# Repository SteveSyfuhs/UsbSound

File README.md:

# Usb Sound
 A custom-made USB sound card for Balanced Audio.

# Why?

My current USB DAC isn't great and instead of just buying a new one I thought I'd try and waste some serious engineering hours learning how to build one instead.

# What's wrong with the current DAC?

My existing DAC uses the [PCM2705](https://www.ti.com/lit/ds/symlink/pcm2705.pdf) chip to handle both the USB and DAC side of things. It's fine, I guess, but it has some annoying quirks.

First, you have to bolt on an additional chip to do silly things like control the USB descriptors. Absent that you're left with this annoying string with two trailing spaces (probably nulls?). Clearly not the end of the world, but I might as well aim for perfect.

Second, the output from the chip is only single-ended so it requires extra effort to make a _good_ differential output. This existing device is using a transformer (two, on per channel) to generate the differential pair, which is great for isolation, but transformers are notorious for distortion at high frequency. 

Curiously this device also doesn't produce a great differential output at 1000hz.

Channel A (blue) is the positive leg and Channel B (red) is the negative leg. Channel 3 (magenta?) is A+B, which ideally should sum to zero, not ~16mV RMS.

# Why are you using X?

To be clear: I really have no idea what I'm doing so my choice of parts or circuit are driven by the last thing I learned about. If there's clearly a better way to do something then please let me know.

### Why the STM32F4 Micro?

It happened to be the chip used in [Phil's video](https://www.youtube.com/watch?v=C7-8nUU6e3E) where learned to use Kicad and it happens to support I2S. It's incredibly powerful for the use case here, and a less powerful device could be used instead. That said, it could make for a useful platform for building out digital filters and stuff.

### Why the [PCM1795](https://www.ti.com/lit/ds/symlink/pcm1795.pdf) DAC?

I like the low distortion and noise floor it provides and since I'm starting with a blank canvas why not start with something that's overkill? I can only make it worse.

Note: the _audible_ differences between this and other DACs is ultimately going to be nil so there will be no notable benefit. I'm doing this because I can.

### Why the [NE5524](https://www.ti.com/lit/ds/symlink/ne5534.pdf) Op-Amps?

The PCM1795 uses that as a baseline for the measured circuits so it's a helpful starting place. I will probably switch these out for [LM4562's](https://www.ti.com/lit/ds/symlink/lm4562.pdf) in the near future once I test out the board and do initial measurements to compare against spec. The LM4562s have lower distortion and noise floor, and more interestingly contain two op-amps in the package so I can reduce the circuit footprint.

Again, I can only make things worse.

### Why Balanced Audio?

The speakers I'll be driving are studio monitors and they require a balanced XLR connection.

## Are you going to support multiple output channels?

Eventually, probably. The micro supports 3 I2S lines, and each I2S line supports two channels out and one in.

## Are you going to support audio in?

Maybe. See the output section.

## What's the driver story?

Ideally it'll show up as a USB audio device and all major operating systems will just pick it up.

# Measurement Methodology

A work in progress. Ideal testing should measure:

 * Noise - Specifically what the device adds to the signal.
 * Distortion - Specifically how the device modifies the signal integrity across the device bandwidth.
 * Flatness - Specifically whether the device has amplified or attenuated voltage across the device bandwidth.

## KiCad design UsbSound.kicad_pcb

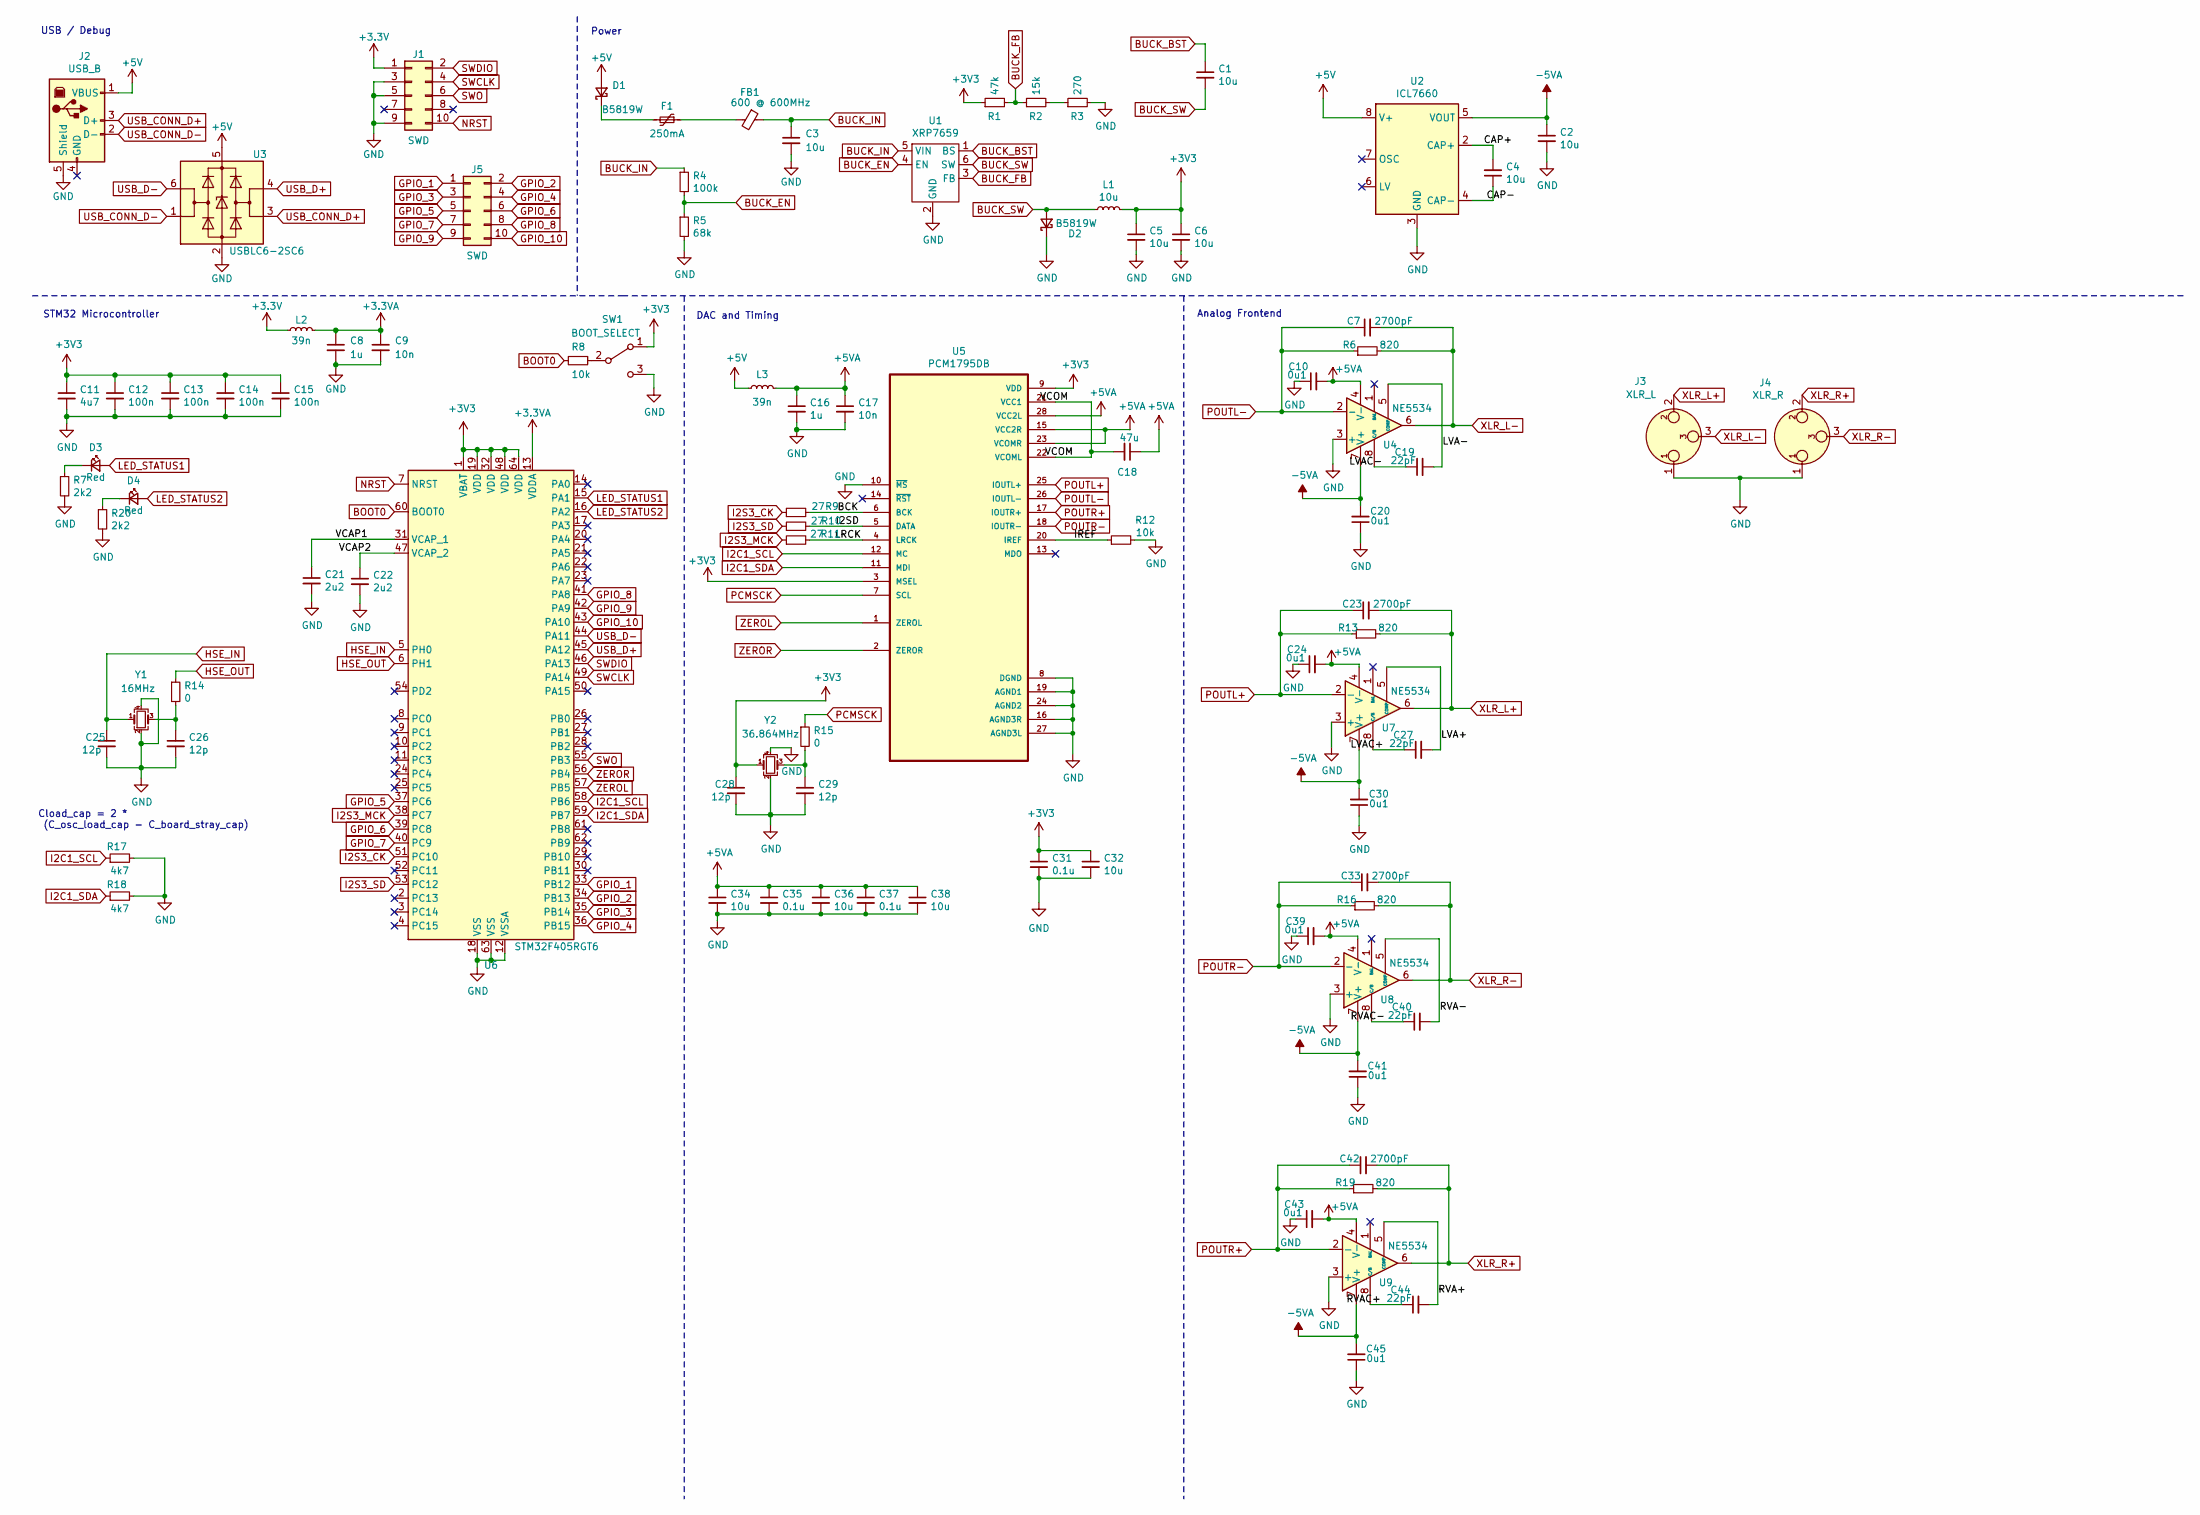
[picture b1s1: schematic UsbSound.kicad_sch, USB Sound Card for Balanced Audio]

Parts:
C1, C2, C4, C5, C6, C32, C34, C36, C38: 10u; C_1206_3216Metric
C3: 10u; C_1206_3216Metric; LCSC Part # C13585
C7, C23, C33, C42: 2700pF; C_1206_3216Metric
C8: 1u; C_1206_3216Metric; LCSC Part # C52923
C9: 10n; C_1206_3216Metric; LCSC Part # C15195
C10, C20, C24, C30, C39, C41, C43, C45: 0u1; C_1206_3216Metric
C11: 4u7; C_1206_3216Metric
C12, C13, C14, C15: 100n; C_1206_3216Metric
C16: 1u; C_1206_3216Metric
C17: 10n; C_1206_3216Metric
C18: 47u; C_1206_3216Metric
C19, C27, C40, C44: 22pF; C_1206_3216Metric
C21, C22: 2u2; C_1206_3216Metric
C25, C26, C28, C29: 12p; C_1206_3216Metric
C31, C35, C37: 0.1u; C_1206_3216Metric
D1: B5819W; D_SOD-123; LCSC Part # C8598
D2: B5819W; D_SOD-123
D3, D4: Red; LED_1206_3216Metric
F1: 250mA; Fuse_1206_3216Metric; LCSC Part # C369159
FB1: 600 @ 600MHz; L_0805_2012Metric; LCSC Part # C1017
J1, J5: SWD; PinHeader_2x05_P1.27mm_Vertical_SMD
J2: USB_B; USB_B_Lumberg_2411_02_Horizontal
J3: XLR_L; Jack_XLR_Neutrik_NC3MAH_Horizontal
J4: XLR_R; Jack_XLR_Neutrik_NC3MAH_Horizontal
L1: 10u; L_1206_3216Metric
L2: 39n; L_0402_1005Metric; LCSC Part # C26443
L3: 39n; L_1206_3216Metric
R1: 47k; R_1206_3216Metric
R2: 15k; R_1206_3216Metric
R3: 270; R_1206_3216Metric
R4: 100k; R_1206_3216Metric
R5: 68k; R_1206_3216Metric
R6, R13, R16, R19: 820; R_1206_3216Metric
R7, R20: 2k2; R_1206_3216Metric
R8, R12: 10k; R_1206_3216Metric
R9, R10, R11: 27; R_1206_3216Metric
R14, R15: 0; R_1206_3216Metric
R17, R18: 4k7; R_1206_3216Metric
SW1: BOOT_SELECT; SW_SPDT_PCM12
U1: XRP7659; TSOP-6_1.65x3.05mm_P0.95mm
U2: ICL7660; SOIC-8-1EP_3.9x4.9mm_P1.27mm_EP2.29x3mm
U3: USBLC6-2SC6; SOT-23-6; LCSC Part # C7519
U4, U7, U8, U9: NE5534; SOIC-8-1EP_3.9x4.9mm_P1.27mm_EP2.29x3mm
U5: PCM1795DB; SOP65P780X200-28N
U6: STM32F405RGT6; LQFP-64_10x10mm_P0.5mm
Y1: 16MHz; Crystal_SMD_3225-4Pin_3.2x2.5mm
Y2: 36.864MHz; Crystal_SMD_3225-4Pin_3.2x2.5mm

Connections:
+3.3VA: C8.1, C9.1, L2.2, U6.13 (VDDA)
+5V: D1.2 (A), J2.1 (VBUS), L3.1, U2.8 (V+), U3.5 (VBUS)
+5VA: C10.2, C16.1, C17.1, C18.1, C24.2, C34.1, C35.1, C36.1, C37.1, C38.1, C39.2, C43.2, L3.2, U4.4 (V-), U5.15 (VCC2R), U5.23 (VCOMR), U5.28 (VCC2L), U7.4 (V-), U8.4 (V-), U9.4 (V-)
-5VA: C2.1, C20.2, C30.2, C41.2, C45.2, U2.5 (VOUT), U4.7 (V+), U7.7 (V+), U8.7 (V+), U9.7 (V+)
/BCK: R9.2, U5.6 (BCK)
/CAP+: C4.2, U2.2 (CAP+)
/CAP-: C4.1, U2.4 (CAP-)
/I2SD: R10.2, U5.5 (DATA)
/IREF: R12.1, U5.20 (IREF)
/LRCK: R11.2, U5.4 (LRCK)
/LVA+: C27.2, U7.5 (COMP)
/LVA-: C19.2, U4.5 (COMP)
/LVAC+: C27.1, U7.8 (C/B)
/LVAC-: C19.1, U4.8 (C/B)
/RVA+: C44.2, U9.5 (COMP)
/RVA-: C40.2, U8.5 (COMP)
/RVAC+: C44.1, U9.8 (C/B)
/RVAC-: C40.1, U8.8 (C/B)
/VCAP1: C21.1, U6.31 (VCAP_1)
/VCAP2: C22.1, U6.47 (VCAP_2)
/VCOM: C18.2, U5.21 (VCC1), U5.22 (VCOML)
BOOT0: R8.2, U6.60 (BOOT0)
BUCK_BST: C1.1, U1.1 (BS)
BUCK_EN: R4.2, R5.1, U1.4 (EN)
BUCK_FB: R1.2, R2.1, U1.3 (FB)
BUCK_IN: C3.1, FB1.1, R4.1, U1.5 (VIN)
BUCK_SW: C1.2, D2.2 (A), L1.1, U1.6 (SW)
GND: C2.2, C3.2, C5.2, C6.2, C8.2, C9.2, C10.1, C11.2, C12.2, C13.2, C14.2, C15.2, C16.2, C17.2, C20.1, C21.2, C22.2, C24.1, C25.2, C26.2, C28.2, C29.2, C30.1, C31.2, C32.2, C34.2, C35.2, C36.2, C37.2, C38.2, C39.1, C41.1, C43.1, C45.1, D2.1 (K), J1.3, J1.5, J1.9, J2.5 (Shield), J3.1, J4.1, R3.2, R5.2, R7.2, R12.2, R17.2, R18.2, R20.2, SW1.3 (C), U1.2 (GND), U2.3 (GND), U3.2 (GND), U4.3 (+), U5.8 (DGND), U5.10 (~MS), U5.16 (AGND3R), U5.19 (AGND1), U5.24 (AGND2), U5.27 (AGND3L), U6.12 (VSSA), U6.18 (VSS), U6.63 (VSS), U7.3 (+), U8.3 (+), U9.3 (+), Y1.2, Y1.4, Y2.2, Y2.4
GPIO_1: J5.1, U6.33 (PB12)
GPIO_2: J5.2, U6.34 (PB13)
GPIO_3: J5.3, U6.35 (PB14)
GPIO_4: J5.4, U6.36 (PB15)
GPIO_5: J5.5, U6.37 (PC6)
GPIO_6: J5.6, U6.39 (PC8)
GPIO_7: J5.7, U6.40 (PC9)
GPIO_8: J5.8, U6.41 (PA8)
GPIO_9: J5.9, U6.42 (PA9)
GPIO_10: J5.10, U6.43 (PA10)
HSE_IN: C25.1, U6.5 (PH0), Y1.1
HSE_OUT: R14.1, U6.6 (PH1)
I2C1_SCL: R17.1, U5.12 (MC), U6.58 (PB6)
I2C1_SDA: R18.1, U5.11 (MDI), U6.59 (PB7)
I2S3_CK: R9.1, U6.51 (PC10)
I2S3_MCK: R11.1, U6.38 (PC7)
I2S3_SD: R10.1, U6.53 (PC12)
LED_STATUS1: D3.2 (A), U6.15 (PA1)
LED_STATUS2: D4.2 (A), U6.16 (PA2)
NRST: J1.10, U6.7 (NRST)
unnamed: C26.1, R14.2, Y1.3
unnamed: C29.1, R15.2, Y2.3
unnamed: D1.1 (K), F1.2
unnamed: D3.1 (K), R7.1
unnamed: D4.1 (K), R20.1
unnamed: F1.1, FB1.2
unnamed: R2.2, R3.1
unnamed: R8.1, SW1.2 (B)
PCMSCK: R15.1, U5.7 (SCL)
POUTL+: C23.1, R13.1, U5.25 (IOUTL+), U7.2 (-)
POUTL-: C7.1, R6.1, U4.2 (-), U5.26 (IOUTL-)
POUTR+: C42.1, R19.1, U5.17 (IOUTR+), U9.2 (-)
POUTR-: C33.1, R16.1, U5.18 (IOUTR-), U8.2 (-)
SWCLK: J1.4, U6.49 (PA14)
SWDIO: J1.2, U6.46 (PA13)
SWO: J1.6, U6.55 (PB3)
USB_CONN_D+: J2.3 (D+), U3.3 (I/O2)
USB_CONN_D-: J2.2 (D-), U3.1 (I/O1)
USB_D+: U3.4 (I/O2), U6.45 (PA12)
USB_D-: U3.6 (I/O1), U6.44 (PA11)
XLR_L+: C23.2, J3.2, R13.2, U7.6
XLR_L-: C7.2, J3.3, R6.2, U4.6
XLR_R+: C42.2, J4.2, R19.2, U9.6
XLR_R-: C33.2, J4.3, R16.2, U8.6
ZEROL: U5.1 (ZEROL), U6.57 (PB5)
ZEROR: U5.2 (ZEROR), U6.56 (PB4)

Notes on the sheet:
Cload_cap = 2 * (C_osc_load_cap - C_board_stray_cap)
USB / Debug
STM32 Microcontroller
Power
DAC and Timing
Analog Frontend

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
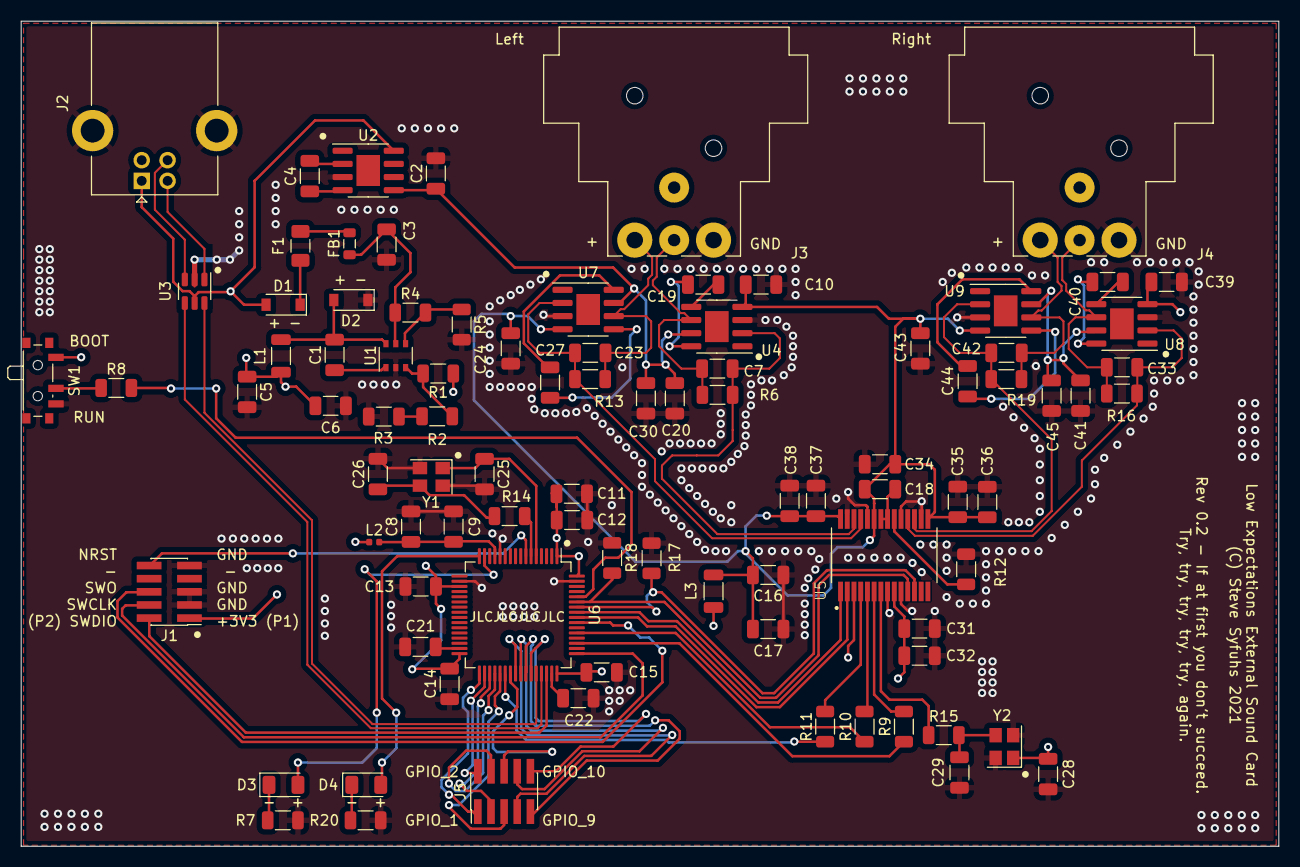
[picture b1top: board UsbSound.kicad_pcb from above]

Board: 4 copper layers, 121.6 x 79.8 mm, 91 parts (0 on the bottom side), 75 nets.

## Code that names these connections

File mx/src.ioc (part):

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Mcu.Name=STM32F405RGTx
Mcu.Package=LQFP64
Mcu.UserName=STM32F405RGTx
PA11.Mode=Device_Only
PA11.Signal=USB_OTG_FS_DM
PA12.Mode=Device_Only
PA12.Signal=USB_OTG_FS_DP
PA13.Mode=Trace_Asynchronous_SW
PA13.Signal=SYS_JTMS-SWDIO
PA14.Mode=Trace_Asynchronous_SW
PA14.Signal=SYS_JTCK-SWCLK
PA4.Mode=Half_Duplex_Master
PA4.Signal=I2S3_WS
PB3.Mode=Trace_Asynchronous_SW
PB3.Signal=SYS_JTDO-SWO
PB4.GPIOParameters=GPIO_Label
PB4.GPIO_Label=ZEROR
PB4.Signal=GPIO_Input
PB5.GPIOParameters=GPIO_Label
PB5.GPIO_Label=ZEROL
PB5.Signal=GPIO_Input
PB6.Mode=I2C
PB6.Signal=I2C1_SCL
PB7.Mode=I2C
PB7.Signal=I2C1_SDA
PC10.Mode=Half_Duplex_Master
PC10.Signal=I2S3_CK
PC12.Mode=Half_Duplex_Master
PC12.Signal=I2S3_SD
PC7.Mode=Master_Clock_Activated
PC7.Signal=I2S3_MCK
PH0-OSC_IN.Mode=HSE-External-Oscillator
PH0-OSC_IN.Signal=RCC_OSC_IN
PH1-OSC_OUT.Mode=HSE-External-Oscillator
PH1-OSC_OUT.Signal=RCC_OSC_OUT
RCC.HSE_VALUE=25000000
RCC.SYSCLKFreq_VALUE=16000000
board=custom

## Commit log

2021-03-30 first pass at schematic.
    Basic USB to micro to DAC to XLR stereo.
    DAC clock needs to be added.
    Power rails for opamps maybe should be boosted.
2021-04-01 fixup electrical rules and stupid grids
    Added crystal for PCM clock.
    Added footprints for most components.
2021-04-03 First rev of board is done
    If at first you don't succeed... try...try...try...try...try...try...try...try...
2021-04-03 Added rev 0.1 fabrication files
2021-04-03 Added image
2021-04-03 Added -5v rail because I'm an idiot and forgot it
2021-04-03 Op Amps are better paired for line matching
2021-04-04 Fixing models
2021-04-04 More via stitching and updated image
2021-04-07 Maybe fixed clock path. Moved some power routes to avoid analog signal.
    Added some additional silkscreen for useful text.
2021-04-07 Initial checkin of firmware -- baseline does nothing.
2021-04-07 Initial checkin of firmware -- baseline does nothing. (actual checkin)
2021-04-07 Added GPIO pin header for future testing
